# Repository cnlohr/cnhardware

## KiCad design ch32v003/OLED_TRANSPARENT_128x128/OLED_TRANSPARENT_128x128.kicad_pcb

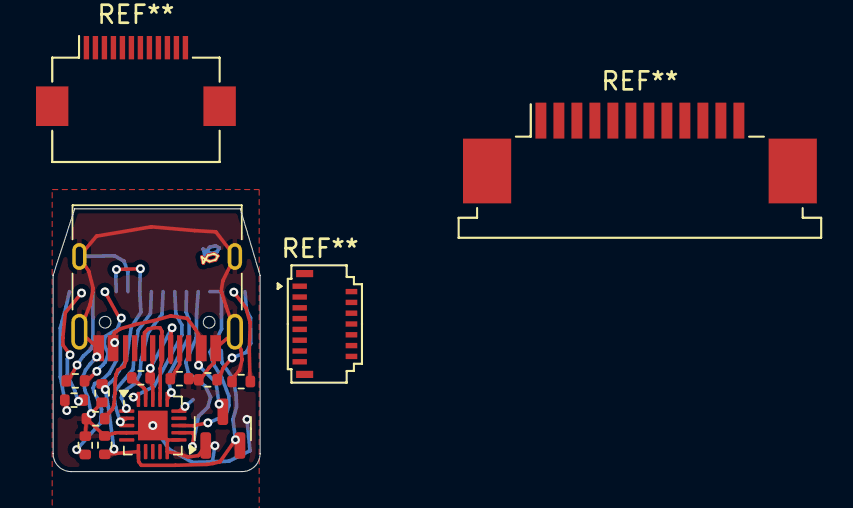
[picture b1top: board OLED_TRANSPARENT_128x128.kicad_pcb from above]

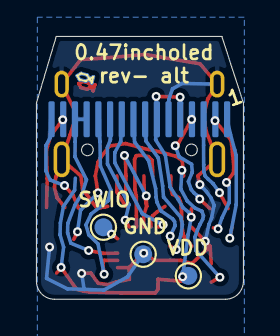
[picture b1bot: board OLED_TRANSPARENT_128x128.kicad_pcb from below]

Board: 2 copper layers, 11.5 x 14.6 mm, 17 parts (4 on the bottom side), 21 nets.

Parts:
C1, C2, C4, C5, C6, C7: 1u; R_0402_1005Metric
C3: 4.7u; R_0402_1005Metric
J2: USB_C_Receptacle_USB2.0; USB_C_Receptacle_HRO_TYPE-C-31-M-12
R3, R4: 5.1k; R_0402_1005Metric
R5: 1.5k; R_0402_1005Metric
TP1: GND; TestPoint_Pad_D1.0mm
TP2: SWIO; TestPoint_Pad_D1.0mm
TP3: VDD; TestPoint_Pad_D1.0mm
U1: P0.65mm_16_pin_OLED_FLEX_CONTACT
U2: CH32V003F4U6; QFN-20-1EP_3x3mm_P0.4mm_EP1.65x1.65mm
U3: XC6206P332MR-G; SOT-23

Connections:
+5V: C3.2, J2.A4 (VBUS), J2.A9 (VBUS), J2.B4 (VBUS), J2.B9 (VBUS), U3.3 (VI)
BS1: U1.8 (BS1), U2.2 (PA1/OSCI/A1/T1CH2/OPN0), U2.3 (PA2/OSCO/A0/T1CH2N/OPP0/AETR2)
CS: U1.9 (CS), U2.1 (PD7/NRST/T2CH4/OPP1/UCK)
D+: J2.A6 (D+), J2.B6 (D+), U2.17 (PD3/A4/T2CH2/AETR/UCTS/T1CH4)
D-: J2.A7 (D-), J2.B7 (D-), R5.2, U2.18 (PD4/A7/UCK/T2CH1ETR/OPO/T1CH4ETR)
DC: U1.11 (D/C), U2.16 (PD2/A3/T1CH1/T2CH3/T1CH2N)
DPU: R5.1, U2.19 (PD5/A5/UTX/T2CH4/URX)
GND: C1.1, C2.1, C3.1, C4.2, C7.2, J2.A1 (GND), J2.A12 (GND), J2.B1 (GND), J2.B12 (GND), J2.S1 (SHIELD), R3.2, R4.2, TP1.1, U1.6 (VSS), U2.4 (VSS), U2.10 (PC3/T1CH3/T1CHIN/UCTS), U2.11 (PC4/A2/T1CH4/MCO/T1CH1CH2N), U2.21 (GND), U3.1 (GND)
unnamed: J2.A5 (CC1), R3.1
unnamed: J2.B5 (CC2), R4.1
unnamed: C6.2, U1.4 (C1N)
unnamed: C6.1, U1.3 (C1P)
unnamed: C5.1, U1.2 (C2N)
unnamed: C5.2, U1.1 (C2P)
unnamed: C4.1, U1.16 (VCC)
unnamed: C7.1, U1.15 (VCOMH)
RST: U1.10 (RES), U2.20 (PD6/A7/URX/T2CH3/UTX)
SCL: U1.12 (D0), U2.12 (PC5/SCK/T1ETR/T2CH1ETR/SCL/UCK/T1CH3)
SDA: U1.13 (D1), U1.14 (D2), U2.13 (PC6/MOSI/T1CH1CH3/UCTS/SDA)
SWIO: TP2.1, U2.15 (PD1/SWIO/AETR/T1CH3/SCL/URX)
VDD: C1.2, C2.2, TP3.1, U1.5 (VBAT), U1.7 (VDD), U2.6 (VDD), U3.2 (VO)

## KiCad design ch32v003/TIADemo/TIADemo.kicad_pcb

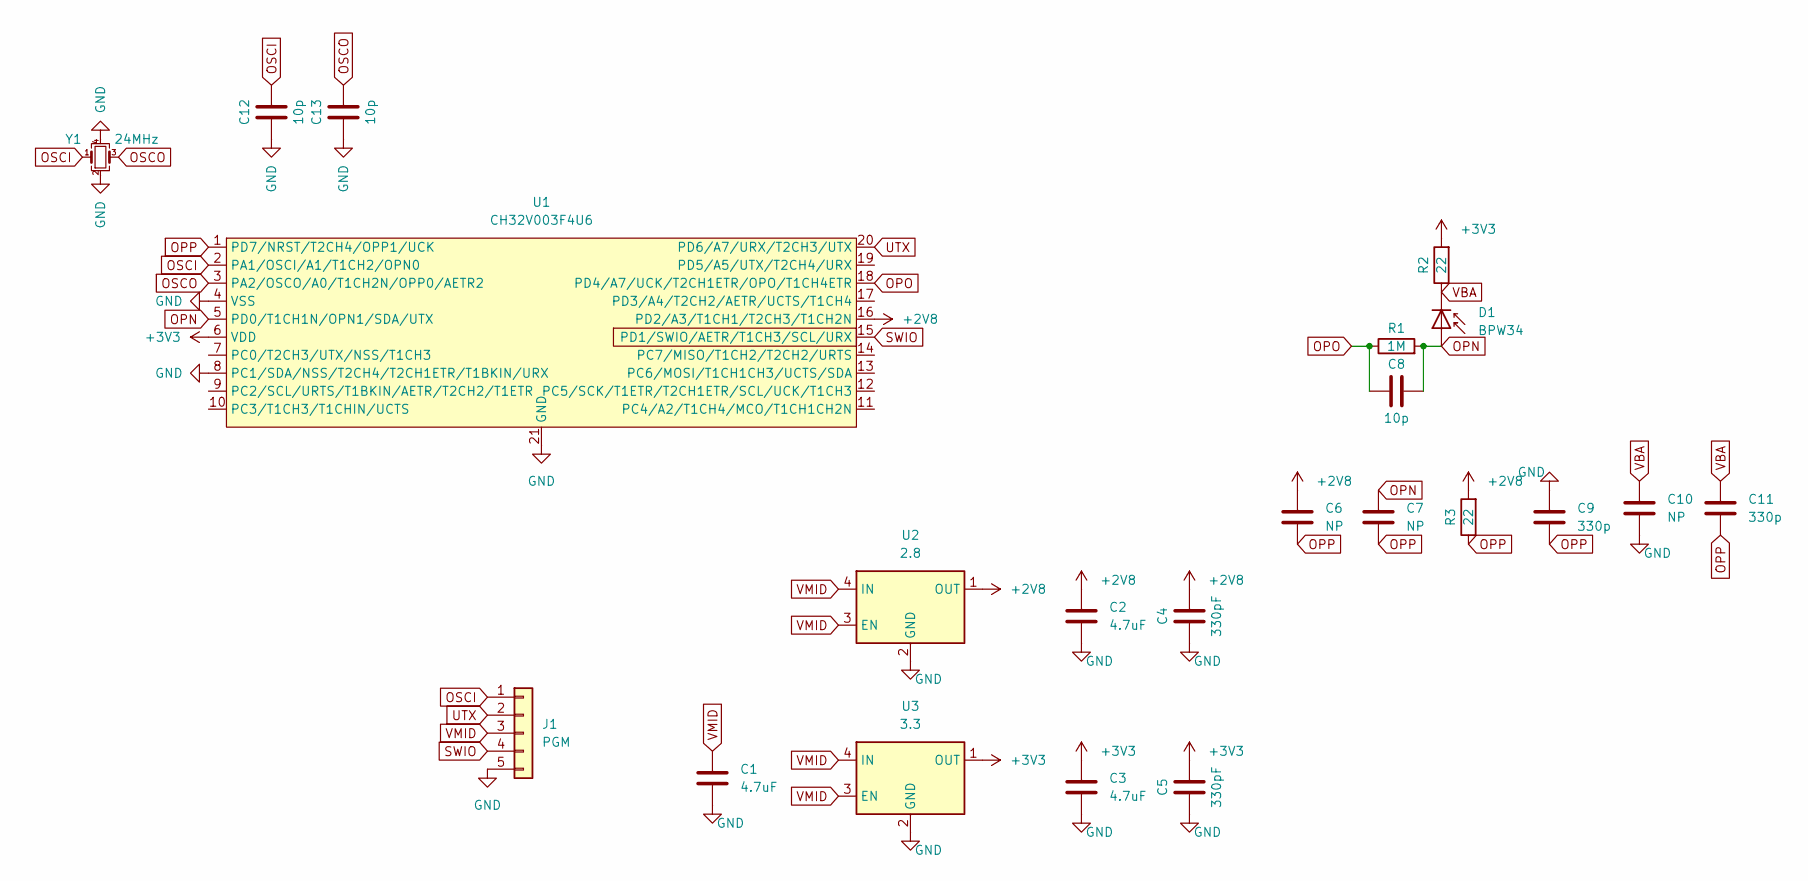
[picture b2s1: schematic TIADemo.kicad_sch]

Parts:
C1, C2, C3: 4.7uF; C_0402_1005Metric; LCSC C23733
C4, C5: 330pF; C_0402_1005Metric; LCSC C13533
C6, C7, C10: NP; C_0402_1005Metric
C8, C12, C13: 10p; C_0402_1005Metric; LCSC C32949
C9, C11: 330p; C_0402_1005Metric; LCSC C13533
D1: BPW34; Osram_BPW34S-SMD; LCSC C962584
J1: PGM; PinHeader_1x05_P2.54mm_Vertical; LCSC C225491
R1: 1M; R_0402_1005Metric; LCSC C26083
R2, R3: 22; R_0402_1005Metric; LCSC C25092
U1: CH32V003F4U6; QFN-20-1EP_3x3mm_P0.4mm_EP1.65x1.65mm; LCSC C5299908
U2: 2.8; xdfn-reg; LCSC C260891
U3: 3.3; xdfn-reg; LCSC C379350
Y1: 24MHz; Crystal_SMD_2016-4Pin_2.0x1.6mm; LCSC C388793

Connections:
+2V8: C2.1, C4.2, C6.1, R3.2, U1.16 (PD2/A3/T1CH1/T2CH3/T1CH2N), U2.1 (OUT)
+3V3: C3.1, C5.2, R2.2, U1.6 (VDD), U3.1 (OUT)
GND: C1.2, C2.2, C3.2, C4.1, C5.1, C9.1, C10.2, C12.1, C13.1, J1.5, U1.4 (VSS), U1.8 (PC1/SDA/NSS/T2CH4/T2CH1ETR/T1BKIN/URX), U1.21 (GND), U2.2 (GND), U2.5 (GND), U3.2 (GND), U3.5 (GND), Y1.2, Y1.4
OPN: C7.1, C8.2, D1.2 (A), R1.2, U1.5 (PD0/T1CH1N/OPN1/SDA/UTX)
OPO: C8.1, R1.1, U1.18 (PD4/A7/UCK/T2CH1ETR/OPO/T1CH4ETR)
OPP: C6.2, C7.2, C9.2, C11.2, R3.1, U1.1 (PD7/NRST/T2CH4/OPP1/UCK)
OSCI: C12.2, J1.1, U1.2 (PA1/OSCI/A1/T1CH2/OPN0), Y1.1
OSCO: C13.2, U1.3 (PA2/OSCO/A0/T1CH2N/OPP0/AETR2), Y1.3
SWIO: J1.4, U1.15 (PD1/SWIO/AETR/T1CH3/SCL/URX)
UTX: J1.2, U1.20 (PD6/A7/URX/T2CH3/UTX)
VBA: C10.1, C11.1, D1.1 (K), R2.1
VMID: C1.1, J1.3, U2.3 (EN), U2.4 (IN), U3.3 (EN), U3.4 (IN)

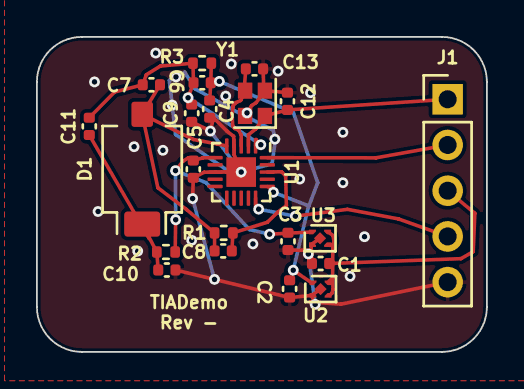
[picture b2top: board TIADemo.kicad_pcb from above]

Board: 2 copper layers, 25.0 x 17.5 mm, 22 parts (0 on the bottom side), 12 nets.

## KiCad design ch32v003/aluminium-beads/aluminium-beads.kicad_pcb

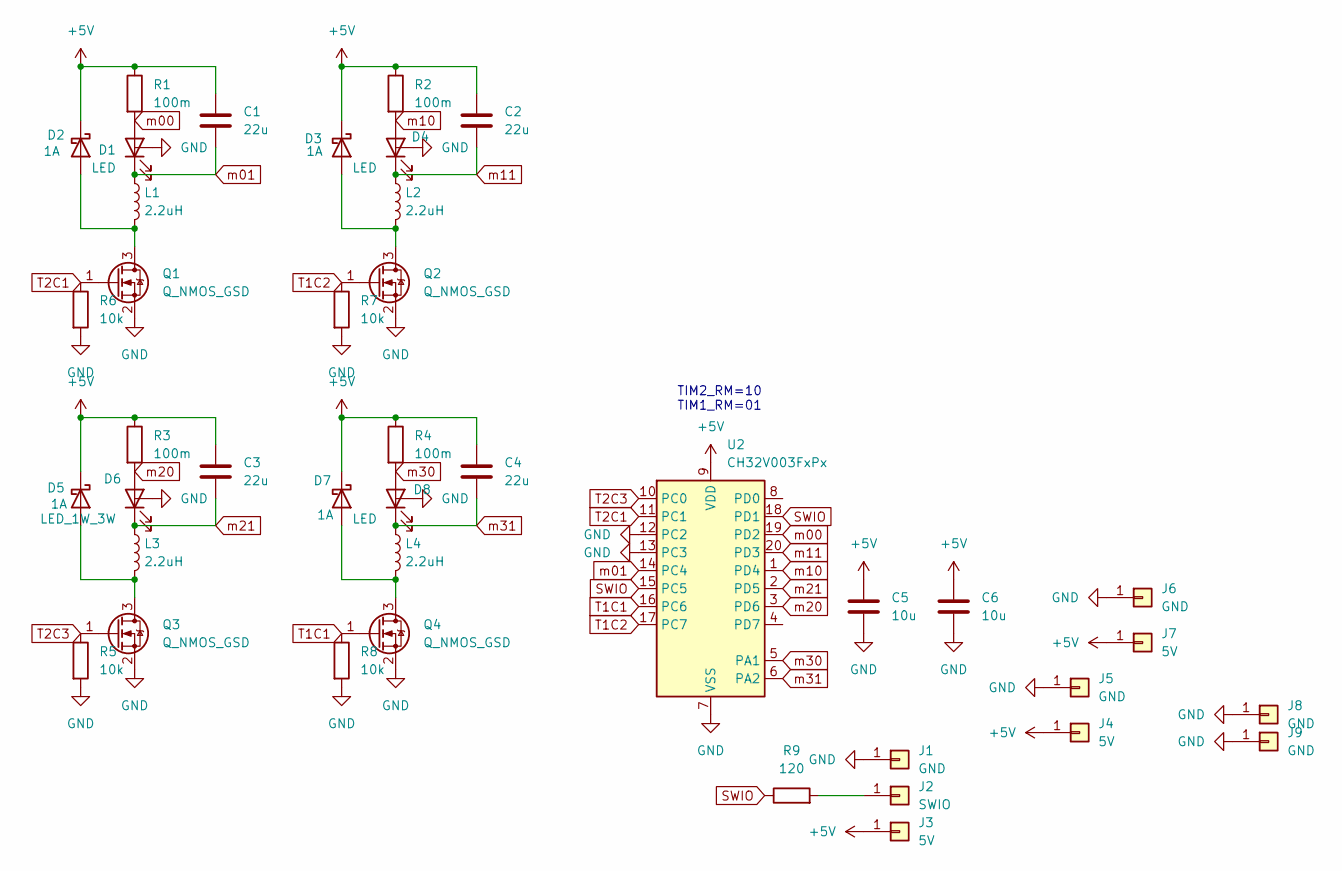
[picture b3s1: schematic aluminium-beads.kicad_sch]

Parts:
C1, C2, C3, C4: 22u; C_1206_3216Metric; LCSC C12891
C5, C6: 10u; C_0805_2012Metric; LCSC C440198
D1, D4, D8: LED; LED_1W_3W_R8-FOR-ALUMINIUM-SUBSTRATE
D2, D3, D5, D7: 1A; D_SOD-323; LCSC C191023
D6: LED_1W_3W; LED_1W_3W_R8-FOR-ALUMINIUM-SUBSTRATE
J1, J5, J6: GND; TestPoint_Pad_1.5x1.5mm
J2: SWIO; TestPoint_Pad_1.5x1.5mm
J3, J4, J7: 5V; TestPoint_Pad_1.5x1.5mm
J8, J9: GND; MountingHole_2.2mm_M2_DIN965_Pad
L1, L2, L3, L4: 2.2uH; L_1008_2520Metric; LCSC C5832372
Q1, Q2, Q3, Q4: Q_NMOS_GSD; SOT-23; LCSC C20917
R1, R2, R3, R4: 100m; R_1206_3216Metric; LCSC C25334
R5, R6, R7, R8: 10k; R_0805_2012Metric; LCSC C17414
R9: 120; R_0805_2012Metric; LCSC C17437
U2: CH32V003FxPx; TSSOP-20_4.4x6.5mm_P0.65mm

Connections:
+5V: C1.1, C2.1, C3.1, C4.1, C5.1, C6.1, D2.1 (K), D3.1 (K), D5.1 (K), D7.1 (K), J3.1, J4.1, J7.1, R1.1, R2.1, R3.1, R4.1, U2.9 (VDD)
GND: C5.2, C6.2, D1.3 (PAD), D4.3 (PAD), D6.3 (PAD), D8.3 (PAD), J1.1, J5.1, J6.1, J8.1, J9.1, Q1.2 (S), Q2.2 (S), Q3.2 (S), Q4.2 (S), R5.2, R6.2, R7.2, R8.2, U2.7 (VSS), U2.12 (PC2), U2.13 (PC3)
unnamed: D2.2 (A), L1.2, Q1.3 (D)
unnamed: D3.2 (A), L2.2, Q2.3 (D)
unnamed: D5.2 (A), L3.2, Q3.3 (D)
unnamed: D7.2 (A), L4.2, Q4.3 (D)
unnamed: J2.1, R9.2
SWIO: R9.1, U2.15 (PC5), U2.18 (PD1)
T1C1: Q4.1 (G), R8.1, U2.16 (PC6)
T1C2: Q2.1 (G), R7.1, U2.17 (PC7)
T2C1: Q1.1 (G), R6.1, U2.11 (PC1)
T2C3: Q3.1 (G), R5.1, U2.10 (PC0)
m00: D1.2 (A), R1.2, U2.19 (PD2)
m01: C1.2, D1.1 (K), L1.1, U2.14 (PC4)
m10: D4.2 (A), R2.2, U2.1 (PD4)
m11: C2.2, D4.1 (K), L2.1, U2.20 (PD3)
m20: D6.2 (A), R3.2, U2.3 (PD6)
m21: C3.2, D6.1 (K), L3.1, U2.2 (PD5)
m30: D8.2 (A), R4.2, U2.5 (PA1)
m31: C4.2, D8.1 (K), L4.1, U2.6 (PA2)

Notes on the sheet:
TIM2_RM=10 TIM1_RM=01

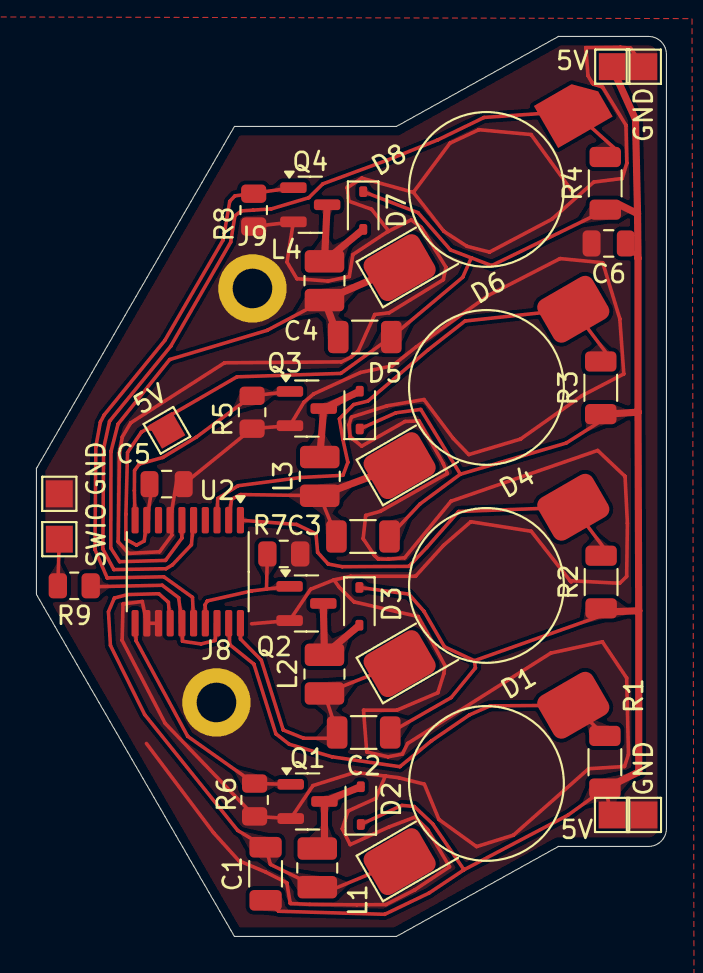
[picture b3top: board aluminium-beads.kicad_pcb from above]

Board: 2 copper layers, 35.0 x 50.0 mm, 41 parts (0 on the bottom side), 20 nets.

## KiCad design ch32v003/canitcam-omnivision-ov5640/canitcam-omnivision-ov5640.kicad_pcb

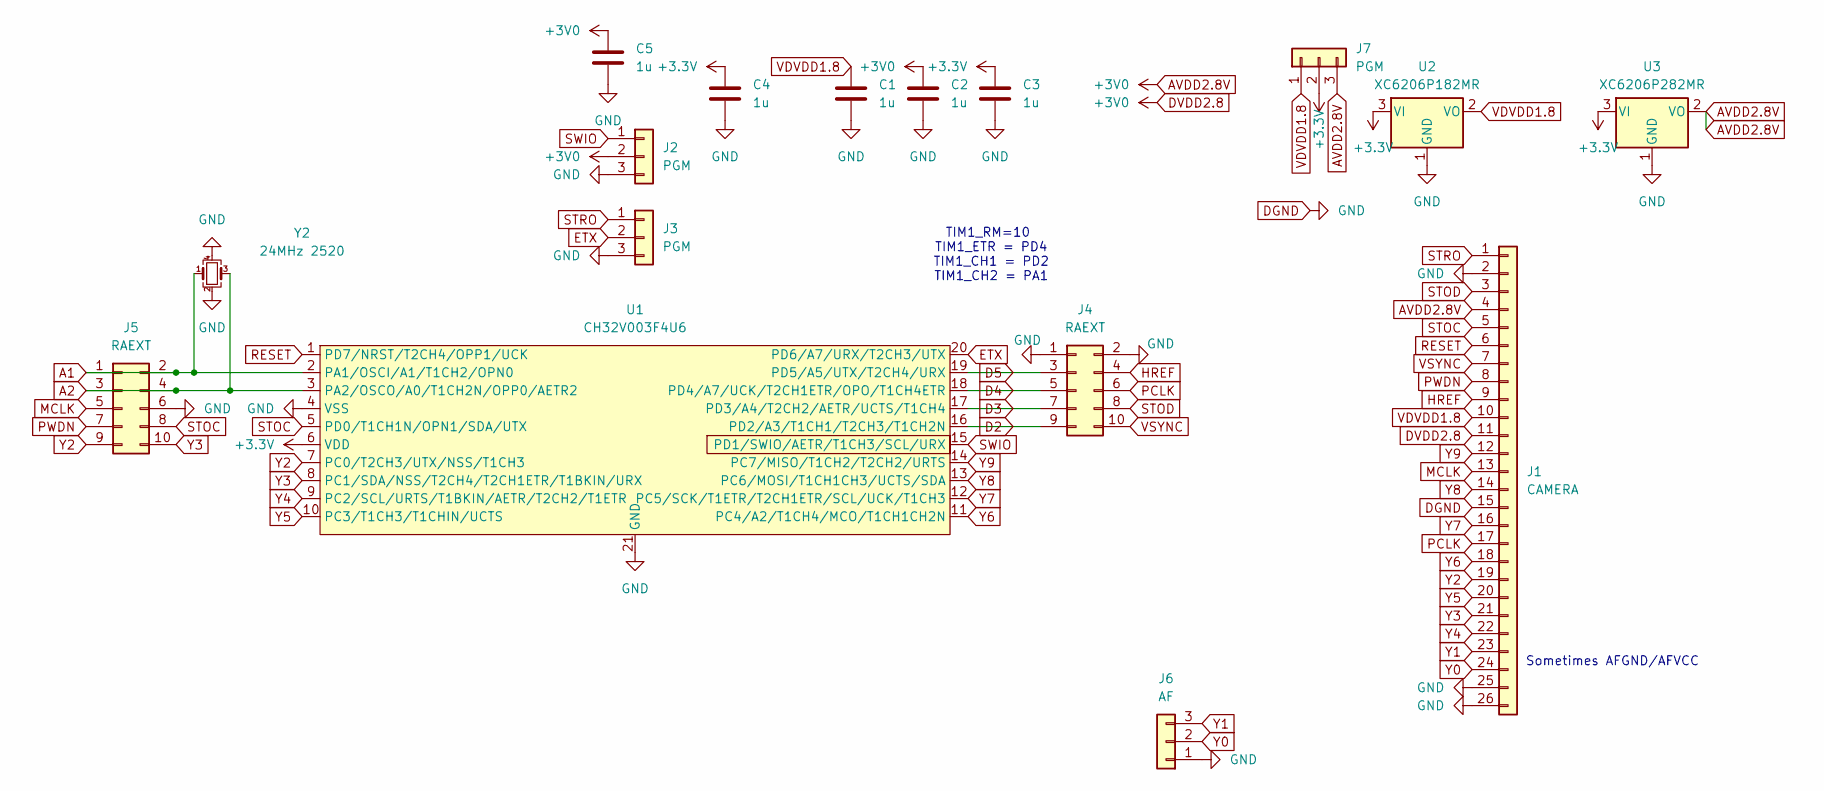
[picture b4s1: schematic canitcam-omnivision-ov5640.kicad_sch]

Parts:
C1, C2, C3, C4, C5: 1u; C_0402_1005Metric; LCSC C52923
J1: CAMERA; XUNPU_FPC-05F-24PH15; LCSC C2856831
J2, J3, J7: PGM; PinHeader_1x03_P2.54mm_Vertical; LCSC C2937625
J4, J5: RAEXT; PinHeader_2x05_P2.54mm_Vertical; LCSC C492422
J6: AF; PinHeader_1x03_P2.54mm_Vertical; LCSC C2937625
U1: CH32V003F4U6; QFN-20-1EP_3x3mm_P0.4mm_EP1.65x1.65mm; LCSC C5299908
U2: XC6206P182MR; SOT-23; LCSC C347373
U3: XC6206P282MR; SOT-23; LCSC C347374
Y2: 24MHz 2520; Crystal_SMD_2520-4Pin_2.5x2.0mm; LCSC C2965580

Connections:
+3.3V: C3.1, C4.1, J7.2, U1.6 (VDD), U2.3 (VI), U3.3 (VI)
A1: J5.1, J5.2, U1.2 (PA1/OSCI/A1/T1CH2/OPN0), Y2.1
A2: J5.3, J5.4, U1.3 (PA2/OSCO/A0/T1CH2N/OPP0/AETR2), Y2.3
AVDD2.8V: C2.1, C5.1, J1.4, J1.11, J2.2, J7.3, U3.2 (VO)
D2: J4.9, U1.16 (PD2/A3/T1CH1/T2CH3/T1CH2N)
D3: J4.7, U1.17 (PD3/A4/T2CH2/AETR/UCTS/T1CH4)
D4: J4.5, U1.18 (PD4/A7/UCK/T2CH1ETR/OPO/T1CH4ETR)
D5: J4.3, U1.19 (PD5/A5/UTX/T2CH4/URX)
DGND: C1.2, C2.2, C3.2, C4.2, C5.2, J1.2, J1.15, J1.25, J1.26, J2.3, J3.3, J4.1, J4.2, J5.6, J6.1, U1.4 (VSS), U1.21 (GND), U2.1 (GND), U3.1 (GND), Y2.2, Y2.4
ETX: J3.2, U1.20 (PD6/A7/URX/T2CH3/UTX)
HREF: J1.9, J4.4
MCLK: J1.13, J5.5
PCLK: J1.17, J4.6
PWDN: J1.8, J5.7
RESET: J1.6, U1.1 (PD7/NRST/T2CH4/OPP1/UCK)
STOC: J1.5, J5.8, U1.5 (PD0/T1CH1N/OPN1/SDA/UTX)
STOD: J1.3, J4.8
STRO: J1.1, J3.1
SWIO: J2.1, U1.15 (PD1/SWIO/AETR/T1CH3/SCL/URX)
VDVDD1.8: C1.1, J1.10, J7.1, U2.2 (VO)
VSYNC: J1.7, J4.10
Y0: J1.24, J6.2
Y1: J1.23, J6.3
Y2: J1.19, J5.9, U1.7 (PC0/T2CH3/UTX/NSS/T1CH3)
Y3: J1.21, J5.10, U1.8 (PC1/SDA/NSS/T2CH4/T2CH1ETR/T1BKIN/URX)
Y4: J1.22, U1.9 (PC2/SCL/URTS/T1BKIN/AETR/T2CH2/T1ETR)
Y5: J1.20, U1.10 (PC3/T1CH3/T1CHIN/UCTS)
Y6: J1.18, U1.11 (PC4/A2/T1CH4/MCO/T1CH1CH2N)
Y7: J1.16, U1.12 (PC5/SCK/T1ETR/T2CH1ETR/SCL/UCK/T1CH3)
Y8: J1.14, U1.13 (PC6/MOSI/T1CH1CH3/UCTS/SDA)
Y9: J1.12, U1.14 (PC7/MISO/T1CH2/T2CH2/URTS)

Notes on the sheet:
Sometimes AFGND/AFVCC
TIM1_RM=10 TIM1_ETR = PD4 TIM1_CH1 = PD2 TIM1_CH2 = PA1

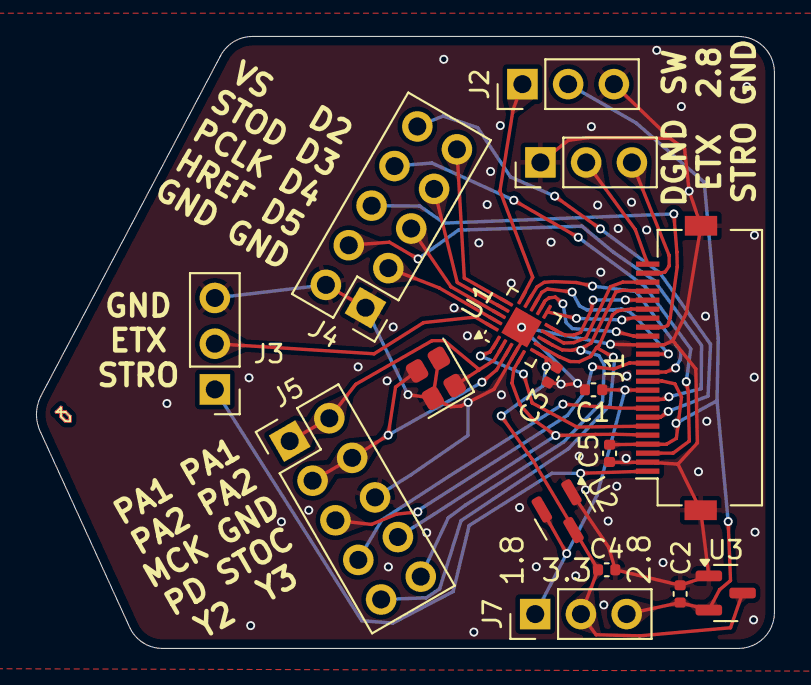
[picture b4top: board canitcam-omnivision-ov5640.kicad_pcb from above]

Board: 2 copper layers, 41.0 x 34.0 mm, 16 parts (0 on the bottom side), 31 nets.

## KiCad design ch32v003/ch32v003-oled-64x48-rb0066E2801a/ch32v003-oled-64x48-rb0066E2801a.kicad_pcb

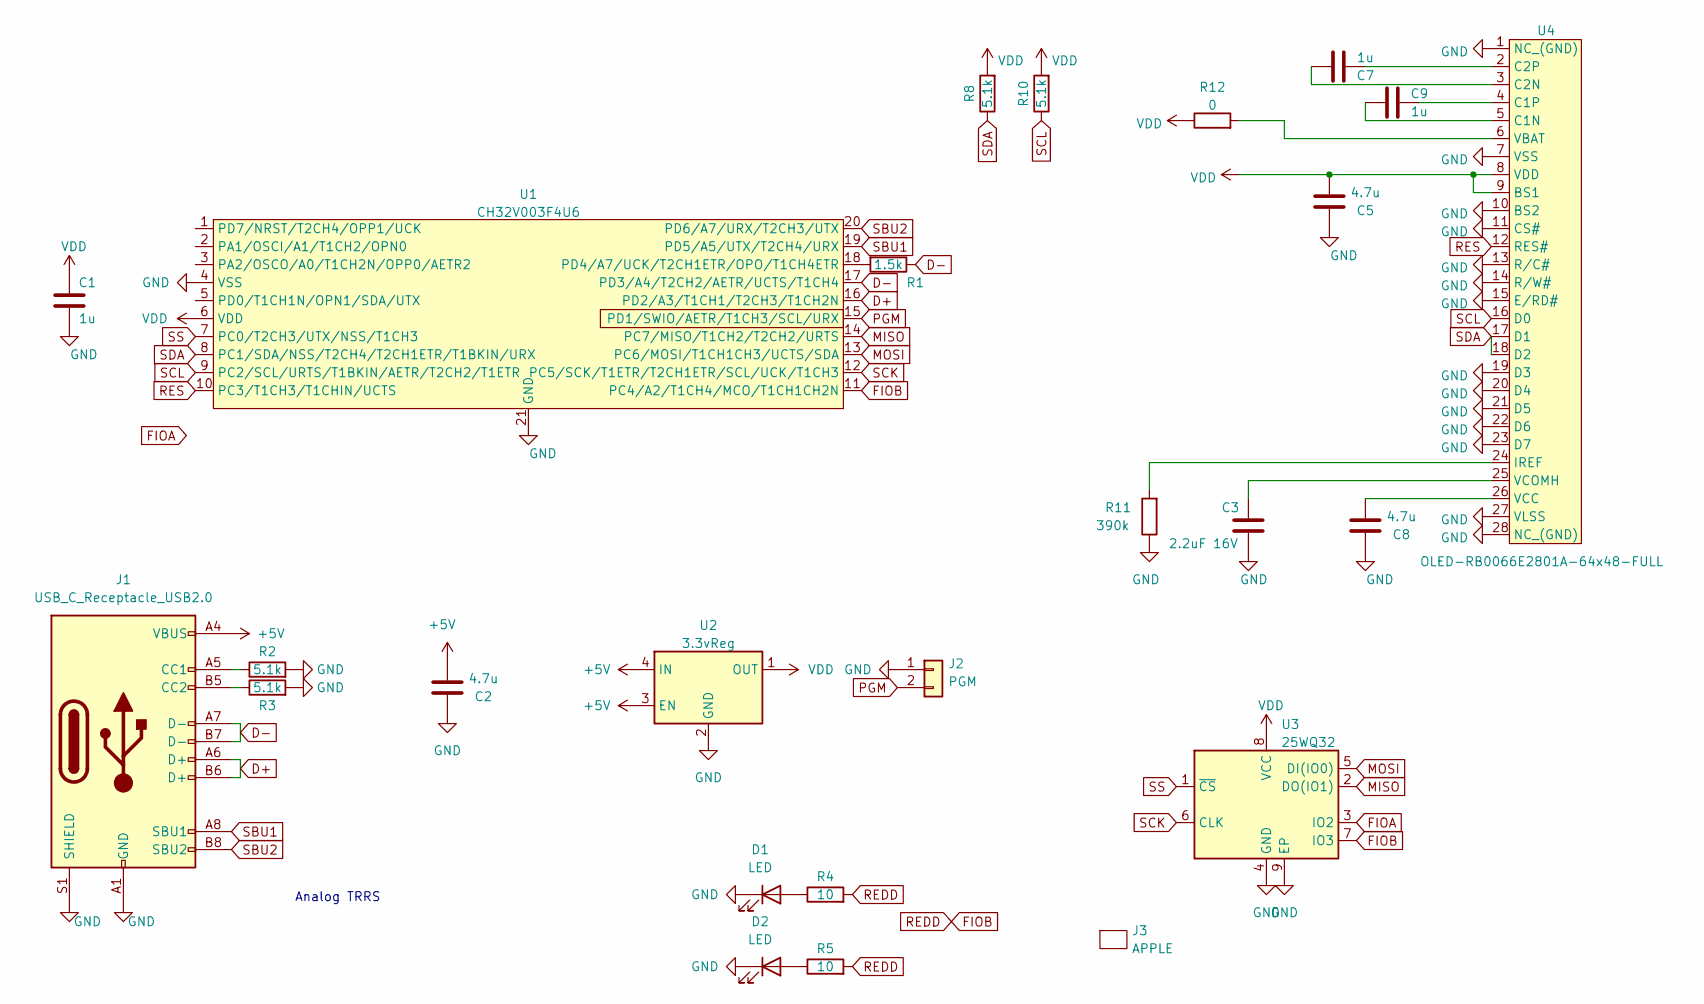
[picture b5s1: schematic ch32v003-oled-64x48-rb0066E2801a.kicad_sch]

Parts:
C1, C7, C9: 1u; R_0402_1005Metric; LCSC C52923
C2, C5, C8: 4.7u; R_0402_1005Metric; LCSC C368809
C3: 2.2uF 16V; R_0402_1005Metric; LCSC C668369
D1, D2: LED; LED_0402_1005Metric; LCSC C74339
J1: USB_C_Receptacle_USB2.0; USB_C_Receptacle_HRO_TYPE-C-31-M-12; LCSC C2765186
J2: PGM; PinHeader_1x03_P2.54mm_Vertical
J3: APPLE; apple
R1: 1.5k; R_0402_1005Metric; LCSC C25867
R2, R3, R8, R10: 5.1k; R_0402_1005Metric; LCSC C25905
R4, R5: 10; R_0402_1005Metric; LCSC C25077
R11: 390k; R_0402_1005Metric; LCSC C163467
R12: 0; R_0402_1005Metric; LCSC C17168
U1: CH32V003F4U6; QFN-20-1EP_3x3mm_P0.4mm_EP1.65x1.65mm; LCSC C5299908
U2: 3.3vReg; xdfn-reg; LCSC C379350
U3: 25WQ32; LCSC NP_C5258281
U4: OLED-RB0066E2801A-64x48-FULL

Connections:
+5V: C2.2, J1.A4 (VBUS), J1.A9 (VBUS), J1.B4 (VBUS), J1.B9 (VBUS), U2.3 (EN), U2.4 (IN)
D+: J1.A6 (D+), J1.B6 (D+), U1.16 (PD2/A3/T1CH1/T2CH3/T1CH2N)
D-: J1.A7 (D-), J1.B7 (D-), R1.1, U1.17 (PD3/A4/T2CH2/AETR/UCTS/T1CH4)
FIOB: R4.2, R5.2, U1.11 (PC4/A2/T1CH4/MCO/T1CH1CH2N), U3.7 (IO3)
GND: C1.1, C2.1, C3.1, C5.1, C8.1, D1.1 (K), D2.1 (K), J1.A1 (GND), J1.A12 (GND), J1.B1 (GND), J1.B12 (GND), J1.S1 (SHIELD), J2.1, R2.2, R3.2, R11.1, U1.4 (VSS), U1.21 (GND), U2.2 (GND), U2.5 (GND), U3.4 (GND), U3.9 (EP), U4.1 (NC_(GND)), U4.7 (VSS), U4.10 (BS2), U4.11 (CS#), U4.13 (R/C#), U4.14 (R/W#), U4.15 (E/RD#), U4.19 (D3), U4.20 (D4), U4.21 (D5), U4.22 (D6), U4.23 (D7), U4.27 (VLSS), U4.28 (NC_(GND))
MISO: U1.14 (PC7/MISO/T1CH2/T2CH2/URTS), U3.2 (DO(IO1))
MOSI: U1.13 (PC6/MOSI/T1CH1CH3/UCTS/SDA), U3.5 (DI(IO0))
unnamed: C3.2, U4.25 (VCOMH)
unnamed: C7.1, U4.3 (C2N)
unnamed: C7.2, U4.2 (C2P)
unnamed: C8.2, U4.26 (VCC)
unnamed: C9.1, U4.5 (C1N)
unnamed: C9.2, U4.4 (C1P)
unnamed: D1.2 (A), R4.1
unnamed: D2.2 (A), R5.1
unnamed: J1.A5 (CC1), R2.1
unnamed: J1.B5 (CC2), R3.1
unnamed: R11.2, U4.24 (IREF)
unnamed: R12.2, U4.6 (VBAT)
unnamed: R1.2, U1.18 (PD4/A7/UCK/T2CH1ETR/OPO/T1CH4ETR)
PGM: J2.2, U1.15 (PD1/SWIO/AETR/T1CH3/SCL/URX)
RES: U1.10 (PC3/T1CH3/T1CHIN/UCTS), U4.12 (RES#)
SBU1: J1.A8 (SBU1), U1.19 (PD5/A5/UTX/T2CH4/URX)
SBU2: J1.B8 (SBU2), U1.20 (PD6/A7/URX/T2CH3/UTX)
SCK: U1.12 (PC5/SCK/T1ETR/T2CH1ETR/SCL/UCK/T1CH3), U3.6 (CLK)
SCL: R10.1, U1.9 (PC2/SCL/URTS/T1BKIN/AETR/T2CH2/T1ETR), U4.16 (D0)
SDA: R8.1, U1.8 (PC1/SDA/NSS/T2CH4/T2CH1ETR/T1BKIN/URX), U4.17 (D1), U4.18 (D2)
SS: U1.7 (PC0/T2CH3/UTX/NSS/T1CH3), U3.1 (~CS)
VDD: C1.2, C5.2, R8.2, R10.2, R12.1, U1.6 (VDD), U2.1 (OUT), U3.8 (VCC), U4.8 (VDD), U4.9 (BS1)

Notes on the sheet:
Analog TRRS

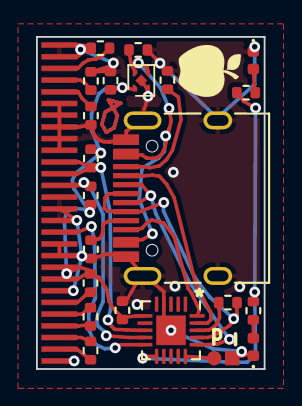
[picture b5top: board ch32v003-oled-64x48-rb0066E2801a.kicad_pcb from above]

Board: 2 copper layers, 12.7 x 18.5 mm, 24 parts (0 on the bottom side), 25 nets.

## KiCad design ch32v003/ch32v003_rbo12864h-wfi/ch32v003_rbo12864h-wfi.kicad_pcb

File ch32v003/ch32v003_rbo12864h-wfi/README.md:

This has moved to rv003usb, under testing/test_lcd_rbo12864h-wfi

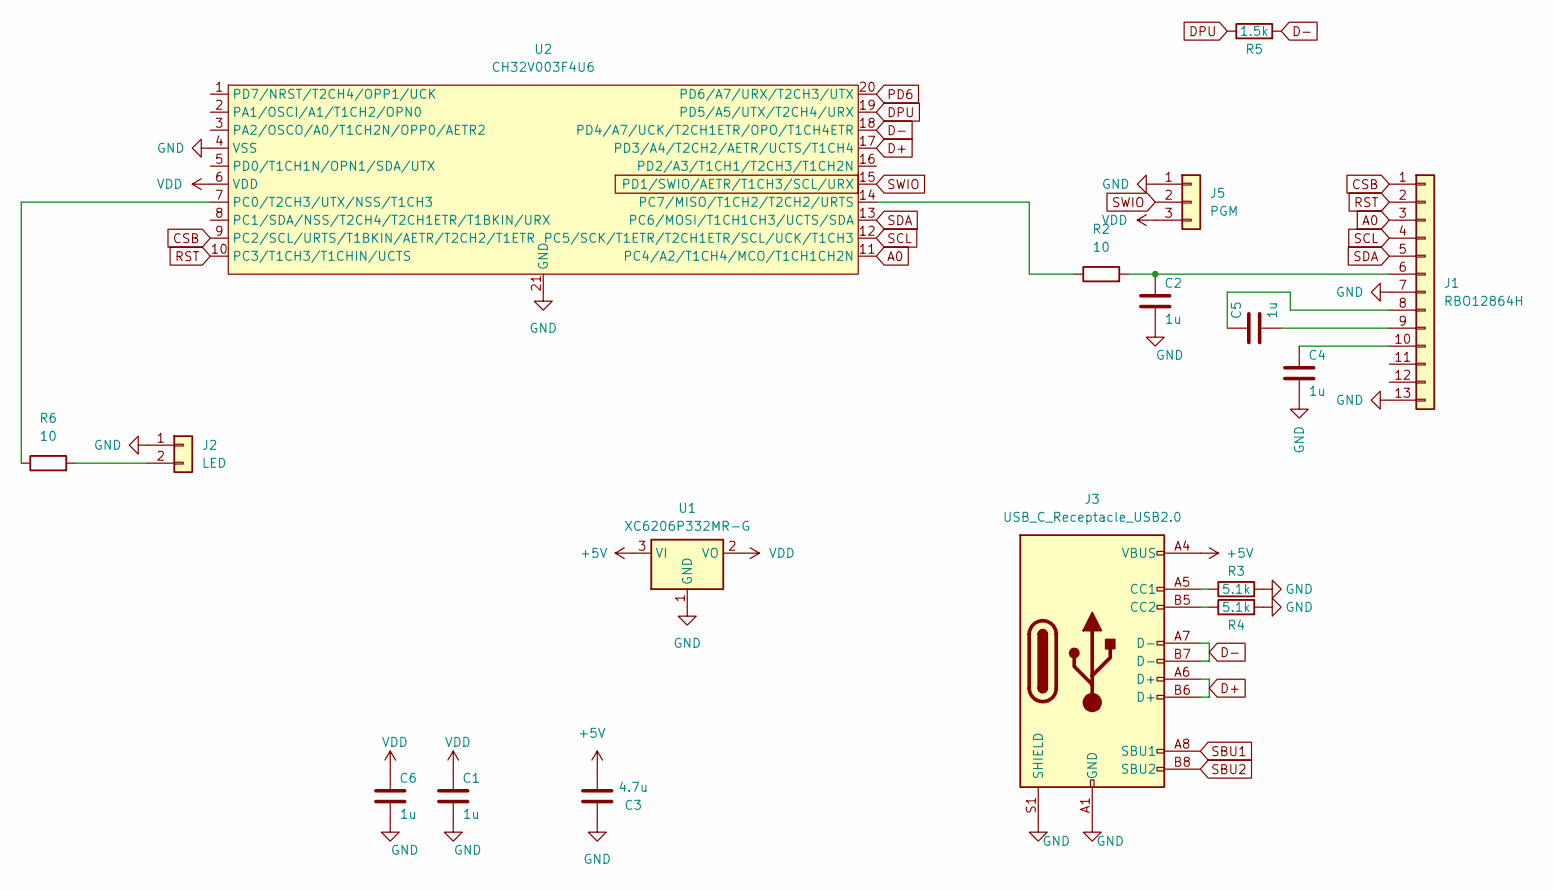
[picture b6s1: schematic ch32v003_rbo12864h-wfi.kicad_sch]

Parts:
C1, C2, C4, C5, C6: 1u; R_0402_1005Metric; LCSC C52923
C3: 4.7u; R_0402_1005Metric; LCSC C368809
J1: RBO12864H; RBO12864H-WFI
J2: LED; PinHeader_1x02_P2.00mm_Vertical
J3: USB_C_Receptacle_USB2.0; USB_C_Receptacle_HRO_TYPE-C-31-M-12; LCSC C2765186
J5: PGM; PinHeader_1x03_P2.54mm_Vertical
R2, R6: 10; R_0402_1005Metric; LCSC C25077
R3, R4: 5.1k; R_0402_1005Metric; LCSC C25905
R5: 1.5k; R_0402_1005Metric; LCSC C25867
U1: XC6206P332MR-G; SOT-23; LCSC C5446
U2: CH32V003F4U6; QFN-20-1EP_3x3mm_P0.4mm_EP1.65x1.65mm; LCSC C5299908

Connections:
+5V: C3.2, J3.A4 (VBUS), J3.A9 (VBUS), J3.B4 (VBUS), J3.B9 (VBUS), U1.3 (VI)
A0: J1.3, U2.11 (PC4/A2/T1CH4/MCO/T1CH1CH2N)
CSB: J1.1, U2.9 (PC2/SCL/URTS/T1BKIN/AETR/T2CH2/T1ETR)
D+: J3.A6 (D+), J3.B6 (D+), U2.17 (PD3/A4/T2CH2/AETR/UCTS/T1CH4)
D-: J3.A7 (D-), J3.B7 (D-), R5.2, U2.18 (PD4/A7/UCK/T2CH1ETR/OPO/T1CH4ETR)
DPU: R5.1, U2.19 (PD5/A5/UTX/T2CH4/URX)
GND: C1.1, C2.1, C3.1, C4.1, C6.1, J1.7, J1.13, J2.1, J3.A1 (GND), J3.A12 (GND), J3.B1 (GND), J3.B12 (GND), J3.S1 (SHIELD), J5.1, R3.2, R4.2, U1.1 (GND), U2.4 (VSS), U2.21 (GND)
unnamed: C2.2, J1.6, R2.2
unnamed: C5.2, J1.8
unnamed: C5.1, J1.9
unnamed: C4.2, J1.10
unnamed: J2.2, R6.2
unnamed: J3.A5 (CC1), R3.1
unnamed: J3.B5 (CC2), R4.1
unnamed: R6.1, U2.7 (PC0/T2CH3/UTX/NSS/T1CH3)
unnamed: R2.1, U2.14 (PC7/MISO/T1CH2/T2CH2/URTS)
PD6: U2.20 (PD6/A7/URX/T2CH3/UTX)
RST: J1.2, U2.10 (PC3/T1CH3/T1CHIN/UCTS)
SBU1: J3.A8 (SBU1)
SBU2: J3.B8 (SBU2)
SCL: J1.4, U2.12 (PC5/SCK/T1ETR/T2CH1ETR/SCL/UCK/T1CH3)
SDA: J1.5, U2.13 (PC6/MOSI/T1CH1CH3/UCTS/SDA)
SWIO: J5.2, U2.15 (PD1/SWIO/AETR/T1CH3/SCL/URX)
VDD: C1.2, C6.2, J5.3, U1.2 (VO), U2.6 (VDD)

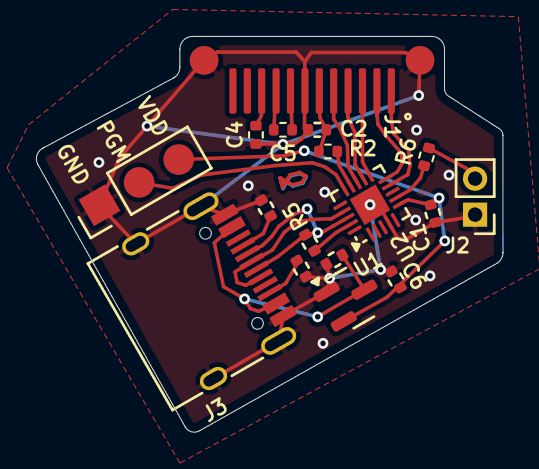
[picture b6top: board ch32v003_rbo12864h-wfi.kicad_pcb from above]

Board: 2 copper layers, 25.9 x 22.0 mm, 17 parts (0 on the bottom side), 21 nets.

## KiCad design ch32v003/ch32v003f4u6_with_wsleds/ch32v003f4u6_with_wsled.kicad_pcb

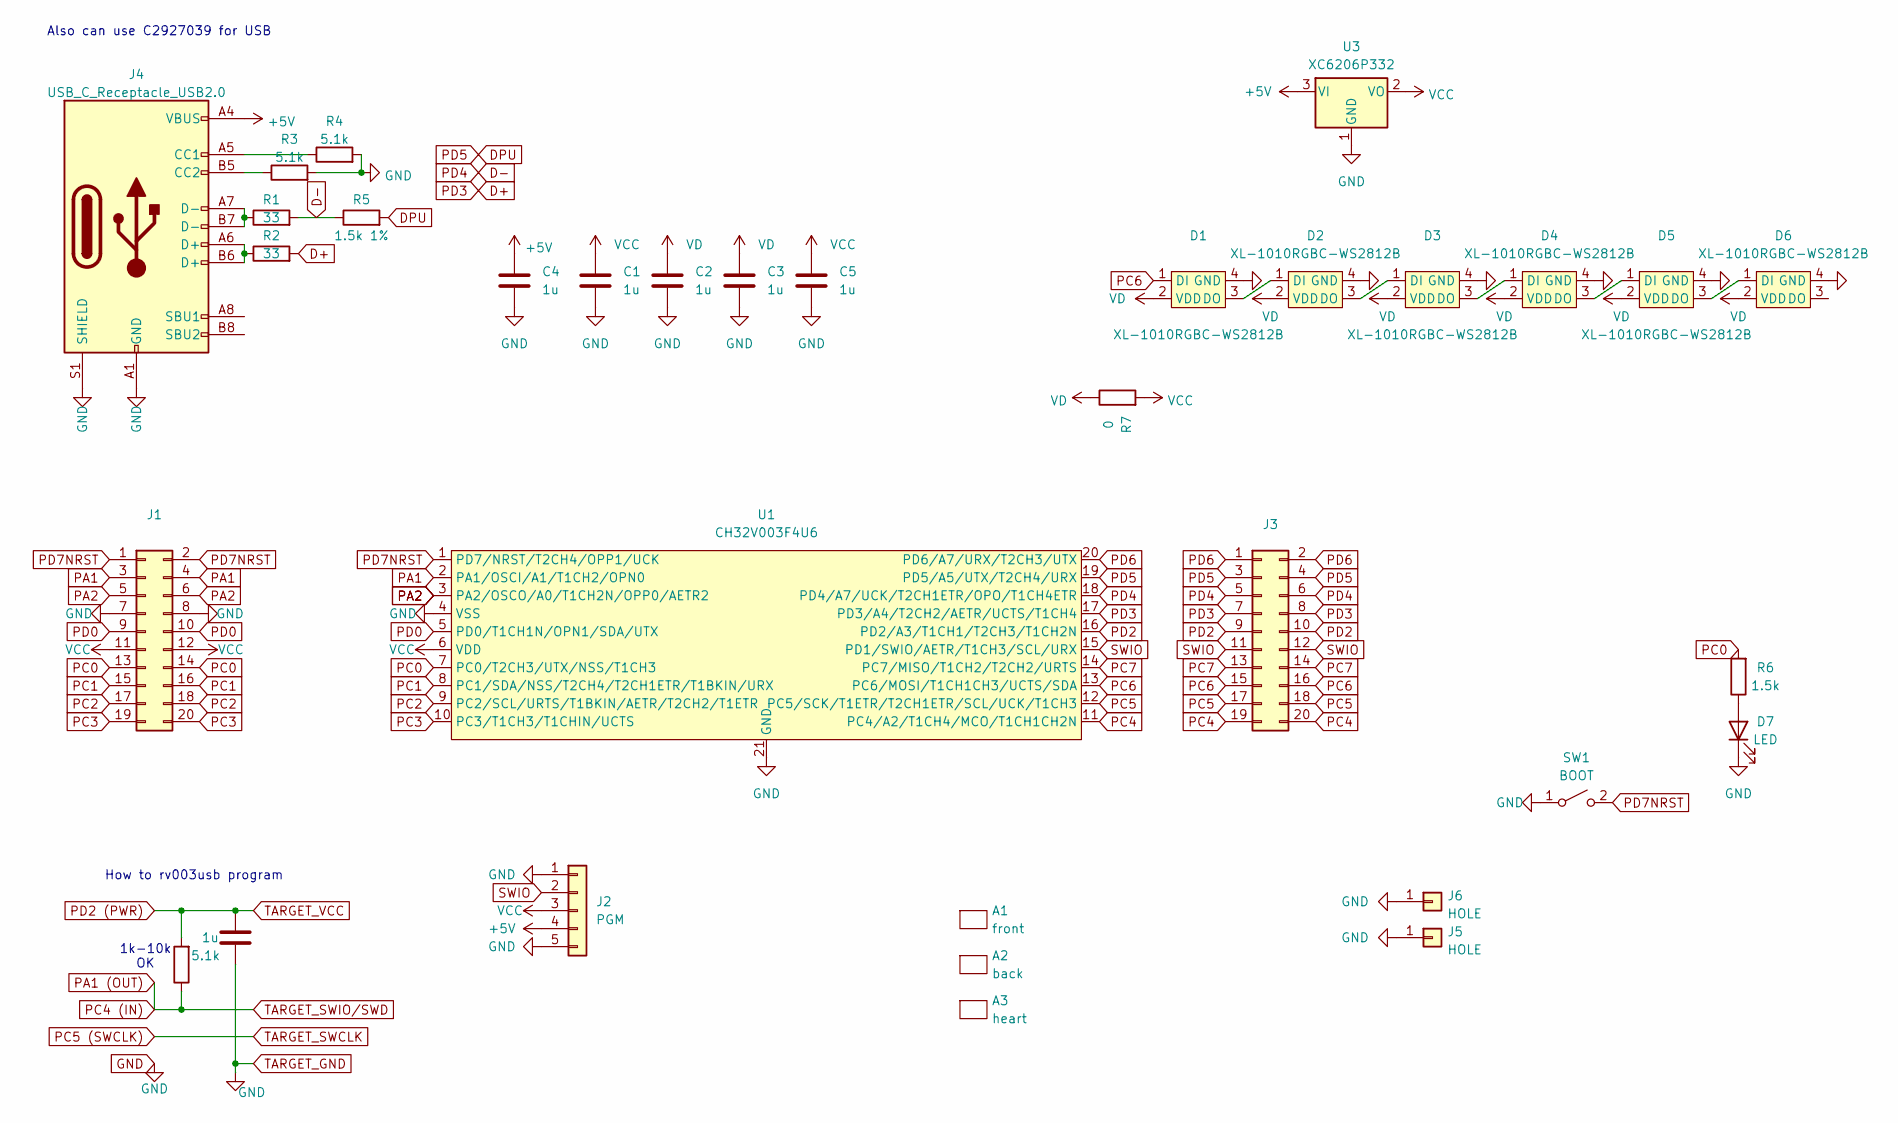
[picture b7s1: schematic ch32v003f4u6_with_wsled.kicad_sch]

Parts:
A1: front; Front
A2: back; Back
A3: heart; Heart
C1, C2, C3, C4, C5, C6: 1u; C_0402_1005Metric; LCSC C15849
D1, D2, D3, D4, D5, D6: XL-1010RGBC-WS2812B; XL-1010RGBC-WS812B; LCSC C5349953
D7: LED; LED_0402_1005Metric; LCSC C74342
J1, J3: PinHeader_2x10_P2.54mm_Vertical; LCSC C124359
J2: PGM; PinHeader_1x05_P2.54mm_Vertical; LCSC C358687
J4: USB_C_Receptacle_USB2.0; USB_C_Receptacle_HRO_TYPE-C-31-M-12; LCSC C709358
J5, J6: HOLE; MountingHole_2.2mm_M2_DIN965_Pad
R1, R2: 33; R_0402_1005Metric; LCSC C25105
R3, R4, R8: 5.1k; R_0402_1005Metric; LCSC C25905
R5: 1.5k 1%; R_0402_1005Metric; LCSC C25867
R6: 1.5k; R_0402_1005Metric; LCSC C25867
R7: 0; R_0402_1005Metric; LCSC C17168
SW1: BOOT; TS-1187A-B-A-B-TACTILE; LCSC C318884
U1: CH32V003F4U6; QFN-20-1EP_3x3mm_P0.4mm_EP1.65x1.65mm; LCSC C5299908
U3: XC6206P332; SOT-23; LCSC C5446

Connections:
+5V: C4.1, J2.4, J4.A4 (VBUS), J4.A9 (VBUS), J4.B4 (VBUS), J4.B9 (VBUS), U3.3 (VI)
D+: J3.7, J3.8, R2.2, U1.17 (PD3/A4/T2CH2/AETR/UCTS/T1CH4)
D-: J3.5, J3.6, R1.2, R5.1, U1.18 (PD4/A7/UCK/T2CH1ETR/OPO/T1CH4ETR)
DPU: J3.3, J3.4, R5.2, U1.19 (PD5/A5/UTX/T2CH4/URX)
GND: C1.2, C2.2, C3.2, C4.2, C5.2, C6.2, D1.4 (GND), D2.4 (GND), D3.4 (GND), D4.4 (GND), D5.4 (GND), D6.4 (GND), D7.1 (K), J1.7, J1.8, J2.1, J2.5, J4.A1 (GND), J4.A12 (GND), J4.B1 (GND), J4.B12 (GND), J4.S1 (SHIELD), J5.1, J6.1, R3.2, R4.2, SW1.1 (A), U1.4 (VSS), U1.21 (GND), U3.1 (GND)
unnamed: C6.1, R8.2
unnamed: D1.3 (DO), D2.1 (DI)
unnamed: D2.3 (DO), D3.1 (DI)
unnamed: D3.3 (DO), D4.1 (DI)
unnamed: D4.3 (DO), D5.1 (DI)
unnamed: D5.3 (DO), D6.1 (DI)
unnamed: D7.2 (A), R6.1
unnamed: J4.A5 (CC1), R4.1
unnamed: J4.B5 (CC2), R3.1
unnamed: J4.A6 (D+), J4.B6 (D+), R2.1
unnamed: J4.A7 (D-), J4.B7 (D-), R1.1
PA1: J1.3, J1.4, U1.2 (PA1/OSCI/A1/T1CH2/OPN0)
PA2: J1.5, J1.6, U1.3 (PA2/OSCO/A0/T1CH2N/OPP0/AETR2)
PC0: J1.13, J1.14, R6.2, U1.7 (PC0/T2CH3/UTX/NSS/T1CH3)
PC1: J1.15, J1.16, U1.8 (PC1/SDA/NSS/T2CH4/T2CH1ETR/T1BKIN/URX)
PC2: J1.17, J1.18, U1.9 (PC2/SCL/URTS/T1BKIN/AETR/T2CH2/T1ETR)
PC3: J1.19, J1.20, U1.10 (PC3/T1CH3/T1CHIN/UCTS)
PC4: J3.19, J3.20, U1.11 (PC4/A2/T1CH4/MCO/T1CH1CH2N)
PC5: J3.17, J3.18, U1.12 (PC5/SCK/T1ETR/T2CH1ETR/SCL/UCK/T1CH3)
PC6: D1.1 (DI), J3.15, J3.16, U1.13 (PC6/MOSI/T1CH1CH3/UCTS/SDA)
PC7: J3.13, J3.14, U1.14 (PC7/MISO/T1CH2/T2CH2/URTS)
PD0: J1.9, J1.10, U1.5 (PD0/T1CH1N/OPN1/SDA/UTX)
PD2: J3.9, J3.10, U1.16 (PD2/A3/T1CH1/T2CH3/T1CH2N)
PD6: J3.1, J3.2, U1.20 (PD6/A7/URX/T2CH3/UTX)
PD7NRST: J1.1, J1.2, SW1.2 (B), U1.1 (PD7/NRST/T2CH4/OPP1/UCK)
SWIO: J2.2, J3.11, J3.12, U1.15 (PD1/SWIO/AETR/T1CH3/SCL/URX)
VCC: C1.1, C5.1, J1.11, J1.12, J2.3, R7.2, U1.6 (VDD), U3.2 (VO)
VD: C2.1, C3.1, D1.2 (VDD), D2.2 (VDD), D3.2 (VDD), D4.2 (VDD), D5.2 (VDD), D6.2 (VDD), R7.1

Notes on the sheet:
Also can use C2927039 for USB
How to rv003usb program
1k-10k OK

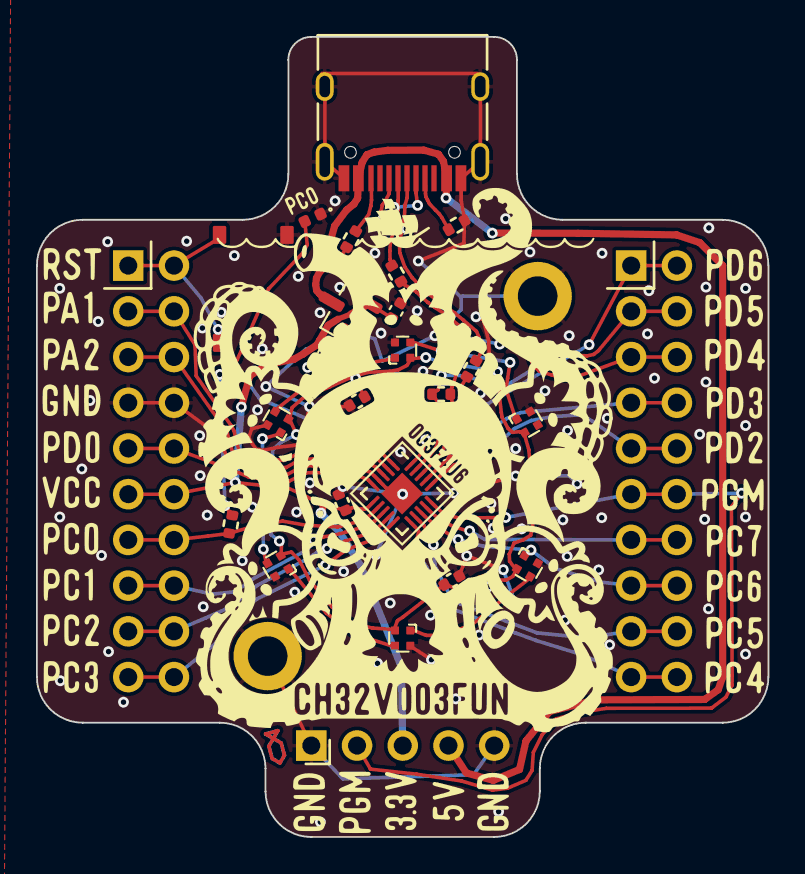
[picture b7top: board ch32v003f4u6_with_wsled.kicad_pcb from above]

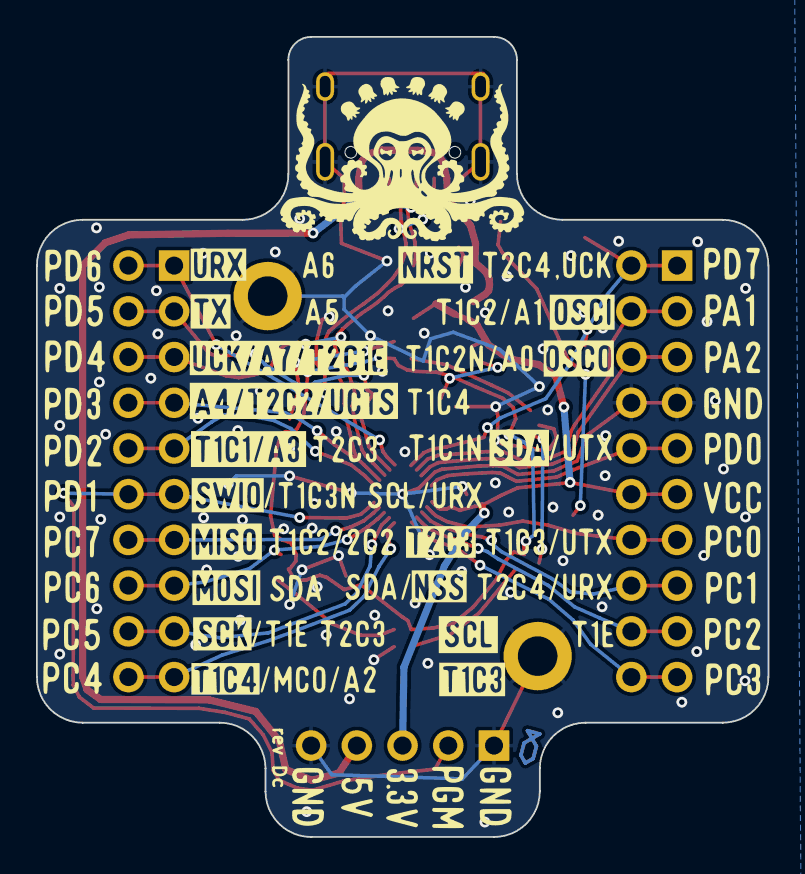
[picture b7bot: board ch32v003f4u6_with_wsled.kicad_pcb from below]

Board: 2 copper layers, 40.6 x 44.5 mm, 31 parts (2 on the bottom side), 32 nets.
